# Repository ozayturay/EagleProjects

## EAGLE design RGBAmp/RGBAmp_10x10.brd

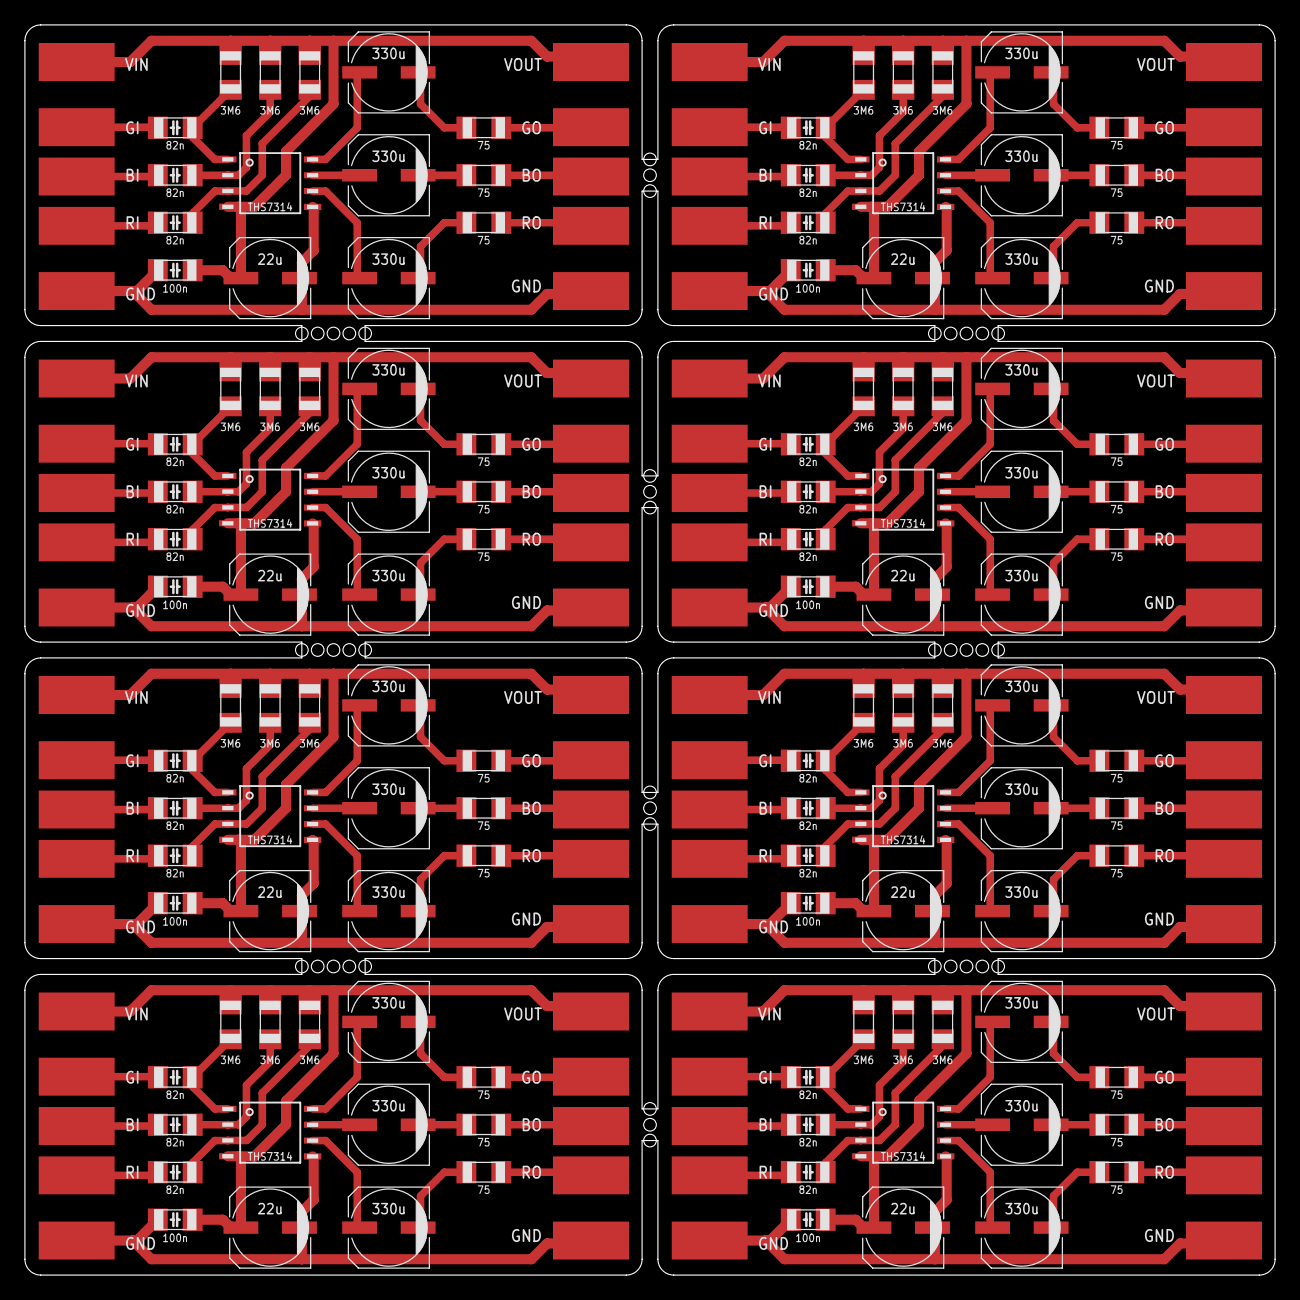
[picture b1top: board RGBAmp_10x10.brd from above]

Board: 2 copper layers, 100.3 x 100.3 mm, 144 parts (8 on the bottom side), 136 nets.

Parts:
C1, C2, C3, C9, C10, C11, C17, C18, C19, C25, C26, C27, C33, C34, C35, C41, C42, C43, C49, C50, C51, C57, C58, C59: 82n; CAPACITOR_CERAMIC_1206
C4, C5, C6, C12, C13, C14, C20, C21, C22, C28, C29, C30, C36, C37, C38, C44, C45, C46, C52, C53, C54, C60, C61, C62: 330u; CAPACITOR_POLARIZED_6.3X7.7
C7, C15, C23, C31, C39, C47, C55, C63: 100n; CAPACITOR_CERAMIC_1206
C8, C16, C24, C32, C40, C48, C56, C64: 22u; CAPACITOR_POLARIZED_6.3X7.7
CN1, CN3, CN5, CN7, CN9, CN11, CN13, CN15: INPUT; GBR_PADS
CN2, CN4, CN6, CN8, CN10, CN12, CN14, CN16: OUTPUT; GBR_PADS
LOGO1, LOGO2, LOGO3, LOGO4, LOGO5, LOGO6, LOGO7, LOGO8: OSHW_LOGO_SMALL
MCU1, MCU2, MCU3, MCU4, MCU5, MCU6, MCU7, MCU8: THS7314; SOP08
R1, R2, R3, R7, R8, R9, R13, R14, R15, R19, R20, R21, R25, R26, R27, R31, R32, R33, R37, R38, R39, R43, R44, R45: 3M6; RESISTOR_1206
R4, R5, R6, R10, R11, R12, R16, R17, R18, R22, R23, R24, R28, R29, R30, R34, R35, R36, R40, R41, R42, R46, R47, R48: 75; RESISTOR_1206

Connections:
GND: C7.2, C8.-, CN1.GND, CN2.GND, MCU1.5
GND1: C15.2, C16.-, CN3.GND, CN4.GND, MCU2.5
GND2: C23.2, C24.-, CN5.GND, CN6.GND, MCU3.5
GND3: C31.2, C32.-, CN7.GND, CN8.GND, MCU4.5
GND4: C39.2, C40.-, CN9.GND, CN10.GND, MCU5.5
GND5: C47.2, C48.-, CN11.GND, CN12.GND, MCU6.5
GND6: C55.2, C56.-, CN13.GND, CN14.GND, MCU7.5
GND7: C63.2, C64.-, CN15.GND, CN16.GND, MCU8.5
unnamed: C1.2, MCU1.1, R1.1
unnamed: C2.2, MCU1.2, R2.1
unnamed: C3.2, MCU1.3, R3.1
unnamed: C2.1, CN1.B
unnamed: C1.1, CN1.G
unnamed: C3.1, CN1.R
unnamed: C4.+, MCU1.8
unnamed: C5.+, MCU1.7
unnamed: C6.+, MCU1.6
unnamed: C4.-, R4.1
unnamed: C5.-, R5.1
unnamed: C6.-, R6.1
unnamed: CN2.G, R4.2
unnamed: CN2.B, R5.2
unnamed: CN2.R, R6.2
unnamed: C9.2, MCU2.1, R7.1
unnamed: C10.2, MCU2.2, R8.1
unnamed: C11.2, MCU2.3, R9.1
unnamed: C10.1, CN3.B
unnamed: C9.1, CN3.G
unnamed: C11.1, CN3.R
unnamed: C12.+, MCU2.8
unnamed: C13.+, MCU2.7
unnamed: C14.+, MCU2.6
unnamed: C12.-, R10.1
unnamed: C13.-, R11.1
unnamed: C14.-, R12.1
unnamed: CN4.G, R10.2
unnamed: CN4.B, R11.2
unnamed: CN4.R, R12.2
unnamed: C17.2, MCU3.1, R13.1
unnamed: C18.2, MCU3.2, R14.1
unnamed: C19.2, MCU3.3, R15.1
unnamed: C18.1, CN5.B
unnamed: C17.1, CN5.G
unnamed: C19.1, CN5.R
unnamed: C20.+, MCU3.8
unnamed: C21.+, MCU3.7
unnamed: C22.+, MCU3.6
unnamed: C20.-, R16.1
unnamed: C21.-, R17.1
unnamed: C22.-, R18.1
unnamed: CN6.G, R16.2
unnamed: CN6.B, R17.2
unnamed: CN6.R, R18.2
unnamed: C25.2, MCU4.1, R19.1
unnamed: C26.2, MCU4.2, R20.1
unnamed: C27.2, MCU4.3, R21.1
unnamed: C26.1, CN7.B
unnamed: C25.1, CN7.G
unnamed: C27.1, CN7.R
unnamed: C28.+, MCU4.8
unnamed: C29.+, MCU4.7
unnamed: C30.+, MCU4.6
unnamed: C28.-, R22.1
unnamed: C29.-, R23.1
unnamed: C30.-, R24.1
unnamed: CN8.G, R22.2
unnamed: CN8.B, R23.2
unnamed: CN8.R, R24.2
unnamed: C33.2, MCU5.1, R25.1
unnamed: C34.2, MCU5.2, R26.1
unnamed: C35.2, MCU5.3, R27.1
unnamed: C34.1, CN9.B
unnamed: C33.1, CN9.G
unnamed: C35.1, CN9.R
unnamed: C36.+, MCU5.8
unnamed: C37.+, MCU5.7
unnamed: C38.+, MCU5.6
unnamed: C36.-, R28.1
unnamed: C37.-, R29.1
unnamed: C38.-, R30.1
unnamed: CN10.G, R28.2
unnamed: CN10.B, R29.2
unnamed: CN10.R, R30.2
unnamed: C41.2, MCU6.1, R31.1
unnamed: C42.2, MCU6.2, R32.1
unnamed: C43.2, MCU6.3, R33.1
unnamed: C42.1, CN11.B
unnamed: C41.1, CN11.G
unnamed: C43.1, CN11.R
unnamed: C44.+, MCU6.8
unnamed: C45.+, MCU6.7
unnamed: C46.+, MCU6.6
unnamed: C44.-, R34.1
unnamed: C45.-, R35.1
unnamed: C46.-, R36.1
unnamed: CN12.G, R34.2
unnamed: CN12.B, R35.2
unnamed: CN12.R, R36.2
unnamed: C49.2, MCU7.1, R37.1
unnamed: C50.2, MCU7.2, R38.1
unnamed: C51.2, MCU7.3, R39.1
unnamed: C50.1, CN13.B
unnamed: C49.1, CN13.G
unnamed: C51.1, CN13.R
unnamed: C52.+, MCU7.8
unnamed: C53.+, MCU7.7
unnamed: C54.+, MCU7.6
unnamed: C52.-, R40.1
unnamed: C53.-, R41.1
unnamed: C54.-, R42.1
unnamed: CN14.G, R40.2
unnamed: CN14.B, R41.2
unnamed: CN14.R, R42.2
unnamed: C57.2, MCU8.1, R43.1
unnamed: C58.2, MCU8.2, R44.1
unnamed: C59.2, MCU8.3, R45.1
unnamed: C58.1, CN15.B
unnamed: C57.1, CN15.G
unnamed: C59.1, CN15.R
unnamed: C60.+, MCU8.8
unnamed: C61.+, MCU8.7
unnamed: C62.+, MCU8.6
unnamed: C60.-, R46.1
unnamed: C61.-, R47.1
unnamed: C62.-, R48.1
unnamed: CN16.G, R46.2
unnamed: CN16.B, R47.2
unnamed: CN16.R, R48.2
VCC: C7.1, C8.+, CN1.VCC, CN2.VCC, MCU1.4, R1.2, R2.2, R3.2
VCC1: C15.1, C16.+, CN3.VCC, CN4.VCC, MCU2.4, R7.2, R8.2, R9.2
VCC2: C23.1, C24.+, CN5.VCC, CN6.VCC, MCU3.4, R13.2, R14.2, R15.2
VCC3: C31.1, C32.+, CN7.VCC, CN8.VCC, MCU4.4, R19.2, R20.2, R21.2
VCC4: C39.1, C40.+, CN9.VCC, CN10.VCC, MCU5.4, R25.2, R26.2, R27.2
VCC5: C47.1, C48.+, CN11.VCC, CN12.VCC, MCU6.4, R31.2, R32.2, R33.2
VCC6: C55.1, C56.+, CN13.VCC, CN14.VCC, MCU7.4, R37.2, R38.2, R39.2
VCC7: C63.1, C64.+, CN15.VCC, CN16.VCC, MCU8.4, R43.2, R44.2, R45.2

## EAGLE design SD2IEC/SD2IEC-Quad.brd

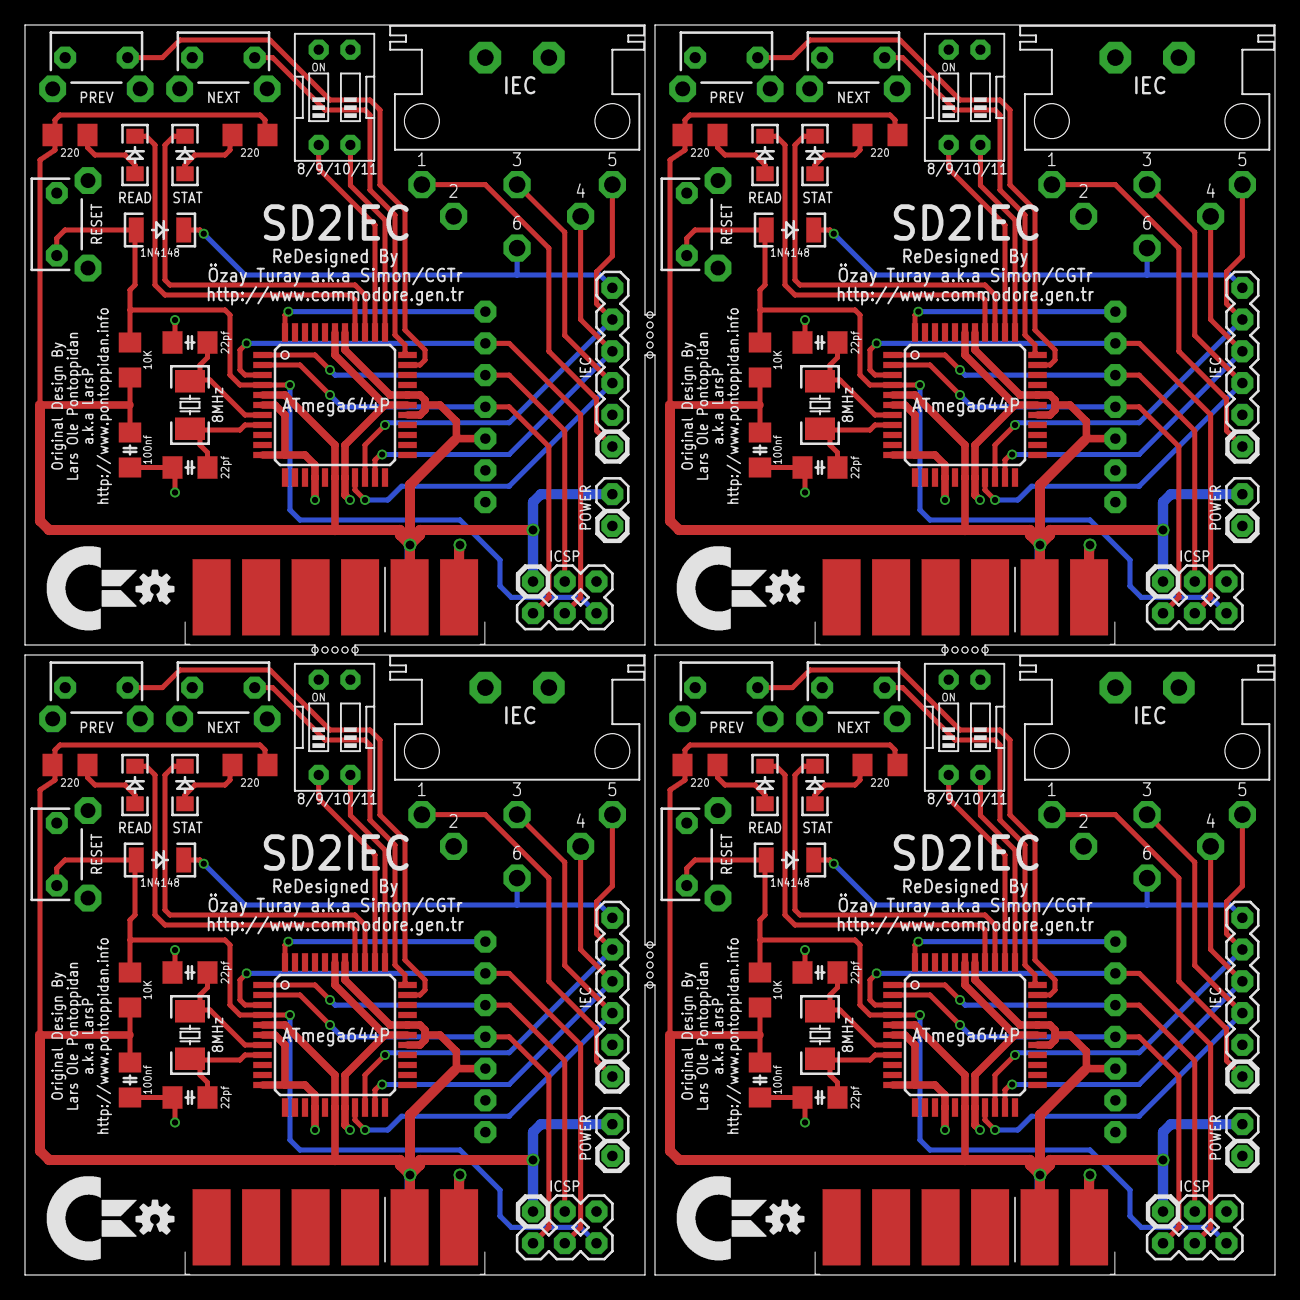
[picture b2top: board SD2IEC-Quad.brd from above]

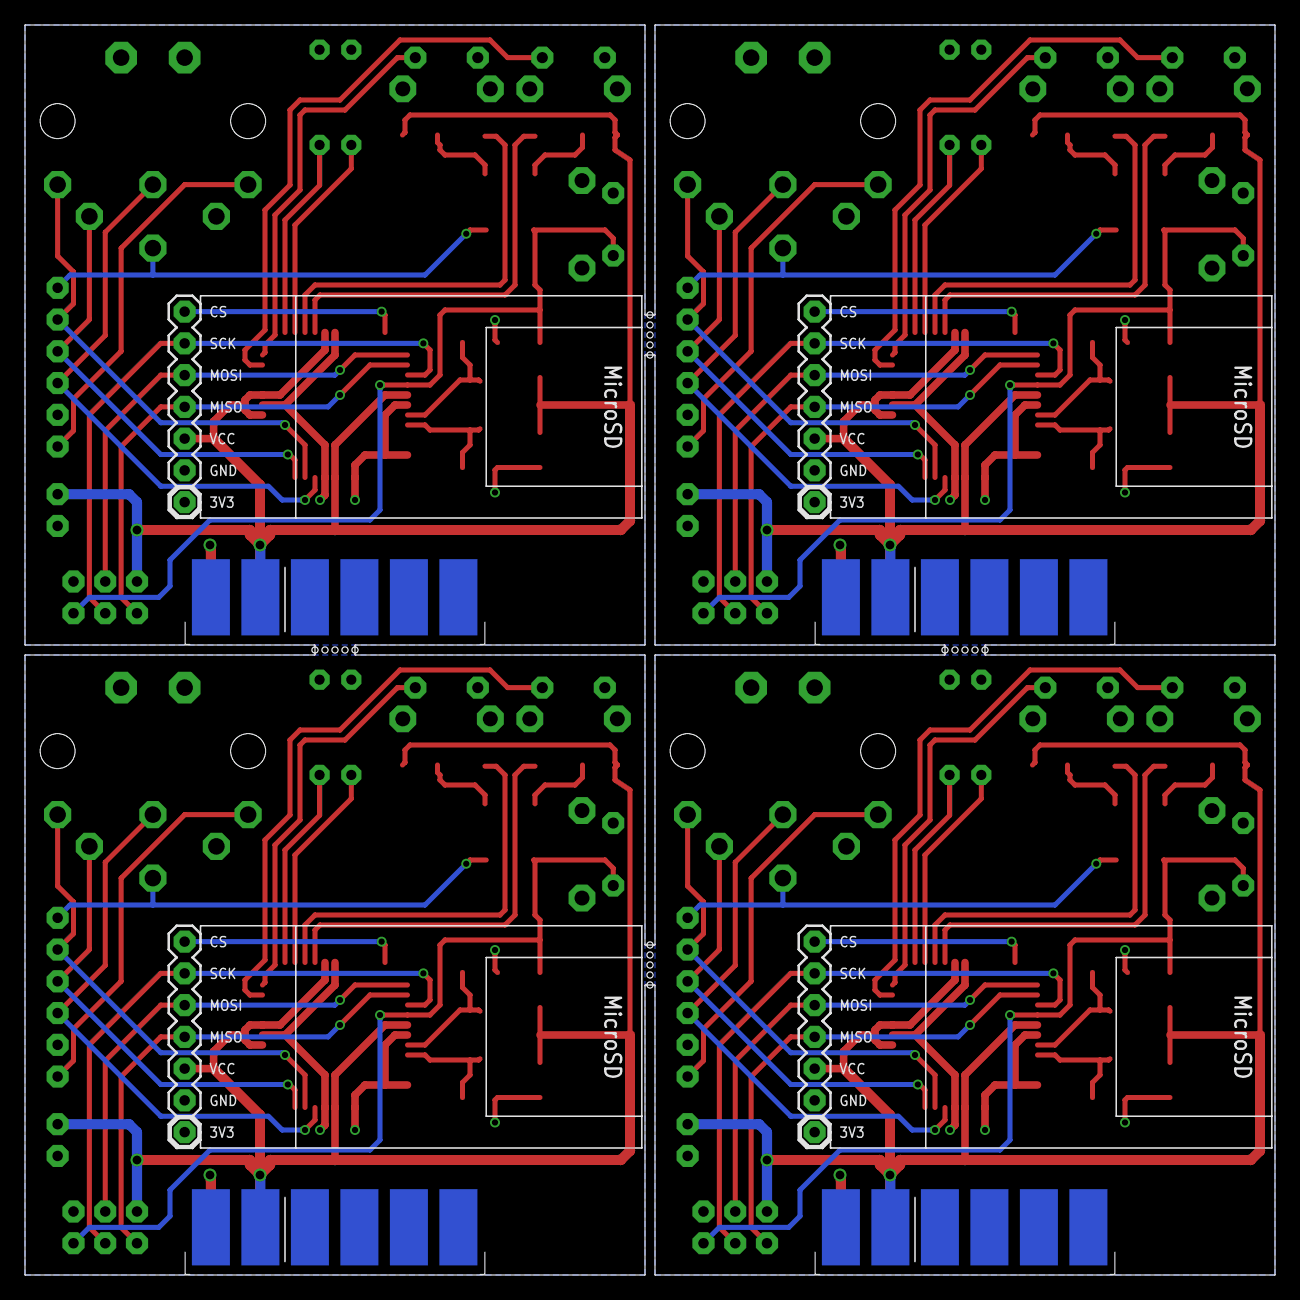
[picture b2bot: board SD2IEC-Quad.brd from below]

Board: 2 copper layers, 100.0 x 100.0 mm, 88 parts (4 on the bottom side), 88 nets.

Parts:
C1, C4, C7, C10: 100nf; CAPACITOR_CERAMIC_1206
C2, C3, C5, C6, C8, C9, C11, C12: 22pf; CAPACITOR_CERAMIC_1206
CN1, CN2, CN3, CN4: DATASETTE; C64_DATASETTE_PADS
D1, D2, D3, D4: 1N4148; DIODE_NORMAL_SMT
J1, J6, J10, J14: POWER; HDR_1X02
J2, J7, J11, J15: IEC; HDR_1X06
J3, J8, J12, J16: ICSP; HDR_2X03
J4, J5, J9, J13: IEC; C64_IEC_DIN6
LED1, LED3, LED5, LED7: STAT; LED_1206
LED2, LED4, LED6, LED8: READ; LED_1206
LOGO1, LOGO2, LOGO3, LOGO4: OSHW_LOGO_SMALL
MCU, MCU1, MCU2, MCU3: ATmega644P; TQFP44
R1, R2, R4, R5, R7, R8, R10, R11: 220; RESISTOR_1206
R3, R6, R9, R12: 10K; RESISTOR_1206
SD, SD1, SD2, SD3: MicroSD; MICROSD_RTL
SW1, SW5, SW9, SW13: NEXT; SWITCH_THT_SIDE
SW2, SW6, SW10, SW14: PREV; SWITCH_THT_SIDE
SW3, SW7, SW11, SW15: RESET; SWITCH_THT_SIDE
SW4, SW8, SW12, SW16: 8/9/10/11; SWITCH_DIP_02
XTAL, XTAL1, XTAL2, XTAL3: 8MHz; XTAL_5032

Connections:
8/1: MCU1.35, SW8.1
8/2: MCU2.35, SW12.1
8/3: MCU3.35, SW16.1
8/9: MCU.35, SW4.1
10/1: MCU1.34, SW8.2
10/2: MCU2.34, SW12.2
10/3: MCU3.34, SW16.2
10/11: MCU.34, SW4.2
CS: MCU.44, SD.CS
CS1: MCU1.44, SD1.CS
CS2: MCU2.44, SD2.CS
CS3: MCU3.44, SD3.CS
GND: C1.1, C2.1, C3.1, CN1.1, CN1.A, J1.1, J2.2, J3.3, J4.2, MCU.6, MCU.11, MCU.15, MCU.18, MCU.28, MCU.39, SD.GND, SW1.2, SW2.2, SW3.1, SW4.3, SW4.4
GND1: C4.1, C5.1, C6.1, CN2.1, CN2.A, J5.2, J6.1, J7.2, J8.3, MCU1.6, MCU1.11, MCU1.15, MCU1.18, MCU1.28, MCU1.39, SD1.GND, SW5.2, SW6.2, SW7.1, SW8.3, SW8.4
GND2: C7.1, C8.1, C9.1, CN3.1, CN3.A, J9.2, J10.1, J11.2, J12.3, MCU2.6, MCU2.11, MCU2.15, MCU2.18, MCU2.28, MCU2.39, SD2.GND, SW9.2, SW10.2, SW11.1, SW12.3, SW12.4
GND3: C10.1, C11.1, C12.1, CN4.1, CN4.A, J13.2, J14.1, J15.2, J16.3, MCU3.6, MCU3.11, MCU3.15, MCU3.18, MCU3.28, MCU3.39, SD3.GND, SW13.2, SW14.2, SW15.1, SW16.3, SW16.4
IEC_ATN: J2.3, J4.3, MCU.19
IEC_ATN1: J5.3, J7.3, MCU1.19
IEC_ATN2: J9.3, J11.3, MCU2.19
IEC_ATN3: J13.3, J15.3, MCU3.19
IEC_CLK: J2.4, J4.4, MCU.21
IEC_CLK1: J5.4, J7.4, MCU1.21
IEC_CLK2: J9.4, J11.4, MCU2.21
IEC_CLK3: J13.4, J15.4, MCU3.21
IEC_DATA: J2.5, J4.5, MCU.20
IEC_DATA1: J5.5, J7.5, MCU1.20
IEC_DATA2: J9.5, J11.5, MCU2.20
IEC_DATA3: J13.5, J15.5, MCU3.20
IEC_RST: D1.C, J2.6, J4.6
IEC_RST1: D2.C, J5.6, J7.6
IEC_RST2: D3.C, J9.6, J11.6
IEC_RST3: D4.C, J13.6, J15.6
IEC_SRQ: J2.1, J4.1
IEC_SRQ1: J5.1, J7.1
IEC_SRQ2: J9.1, J11.1
IEC_SRQ3: J13.1, J15.1
MISO: J3.4, MCU.2, SD.MISO
MISO1: J8.4, MCU1.2, SD1.MISO
MISO2: J12.4, MCU2.2, SD2.MISO
MISO3: J16.4, MCU3.2, SD3.MISO
MOSI: J3.2, MCU.1, SD.MOSI
MOSI1: J8.2, MCU1.1, SD1.MOSI
MOSI2: J12.2, MCU2.1, SD2.MOSI
MOSI3: J16.2, MCU3.1, SD3.MOSI
NEXT: MCU.33, SW1.1
NEXT1: MCU1.33, SW5.1
NEXT2: MCU2.33, SW9.1
NEXT3: MCU3.33, SW13.1
PREV: MCU.32, SW2.1
PREV1: MCU1.32, SW6.1
PREV2: MCU2.32, SW10.1
PREV3: MCU3.32, SW14.1
READ: LED2.C, MCU.37
READ1: LED2.A, R2.1
READ2: LED4.C, MCU1.37
READ3: LED4.A, R5.1
READ4: LED6.C, MCU2.37
READ5: LED6.A, R8.1
READ6: LED8.C, MCU3.37
READ7: LED8.A, R11.1
RST: D1.A, J3.6, MCU.4, R3.2, SW3.2
RST1: D2.A, J8.6, MCU1.4, R6.2, SW7.2
RST2: D3.A, J12.6, MCU2.4, R9.2, SW11.2
RST3: D4.A, J16.6, MCU3.4, R12.2, SW15.2
SCK: J3.5, MCU.3, SD.SCK
SCK1: J8.5, MCU1.3, SD1.SCK
SCK2: J12.5, MCU2.3, SD2.SCK
SCK3: J16.5, MCU3.3, SD3.SCK
SELECT: LED1.C, MCU.36
SELECT1: LED1.A, R1.1
SELECT2: LED3.C, MCU1.36
SELECT3: LED3.A, R4.1
SELECT4: LED5.C, MCU2.36
SELECT5: LED5.A, R7.1
SELECT6: LED7.C, MCU3.36
SELECT7: LED7.A, R10.1
VCC: C1.2, CN1.2, CN1.B, J1.2, J3.1, MCU.5, MCU.17, MCU.27, MCU.29, MCU.38, R1.2, R2.2, R3.1, SD.VCC
VCC1: C4.2, CN2.2, CN2.B, J6.2, J8.1, MCU1.5, MCU1.17, MCU1.27, MCU1.29, MCU1.38, R4.2, R5.2, R6.1, SD1.VCC
VCC2: C7.2, CN3.2, CN3.B, J10.2, J12.1, MCU2.5, MCU2.17, MCU2.27, MCU2.29, MCU2.38, R7.2, R8.2, R9.1, SD2.VCC
VCC3: C10.2, CN4.2, CN4.B, J14.2, J16.1, MCU3.5, MCU3.17, MCU3.27, MCU3.29, MCU3.38, R10.2, R11.2, R12.1, SD3.VCC
XTAL1: C2.2, MCU.8, XTAL.1
XTAL2: C3.2, MCU.7, XTAL.2
XTAL3: C5.2, MCU1.8, XTAL1.1
XTAL4: C6.2, MCU1.7, XTAL1.2
XTAL5: C8.2, MCU2.8, XTAL2.1
XTAL6: C9.2, MCU2.7, XTAL2.2
XTAL7: C11.2, MCU3.8, XTAL3.1
XTAL8: C12.2, MCU3.7, XTAL3.2

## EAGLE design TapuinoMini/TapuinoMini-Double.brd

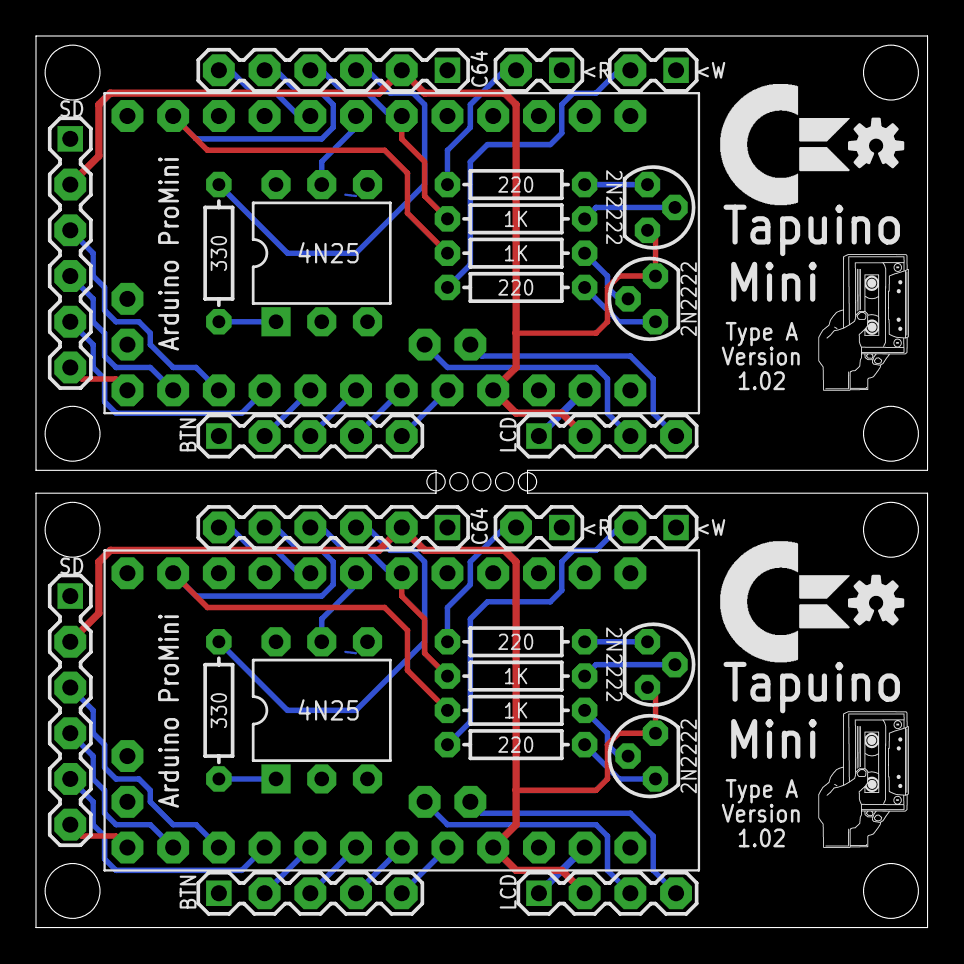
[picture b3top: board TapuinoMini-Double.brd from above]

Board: 2 copper layers, 49.5 x 49.5 mm, 32 parts (0 on the bottom side), 48 nets.

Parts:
IC1, IC2: Arduino ProMini; PROMINI_A
JP1, JP7: LCD; 1X04_SQR
JP2, JP8: SD; 1X06_SQR
JP3, JP9: BTN; 1X05_SQR
JP4, JP10: C64; 1X06_SQR
JP5, JP11: <R; 1X02_SQR
JP6, JP12: <W; 1X02_SQR
OK1, OK2: 4N25; DIP06
Q1, Q2, Q3, Q4: 2N2222; TO-92
R1, R2, R7, R8: 1K; RESISTOR_PTH_0.3
R3, R4, R9, R10: 220; RESISTOR_PTH_0.3
R5, R6: 330; RESISTOR_PTH_0.3
U$1, U$3: OSHW-LOGO-S

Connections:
ABORT: IC1.A2, JP3.4
ABORT1: IC2.A2, JP9.4
CS: IC1.10*, JP2.6
CS1: IC2.10*, JP8.6
GND: IC1.GND@1, JP1.1, JP2.1, JP3.1, JP4.1, JP5.1, JP6.1, OK1.2, OK1.4
GND1: IC2.GND@1, JP7.1, JP8.1, JP9.1, JP10.1, JP11.1, JP12.1, OK2.2, OK2.4
MISO: IC1.12, JP2.3
MISO1: IC2.12, JP8.3
MOSI: IC1.11*, JP2.4
MOSI1: IC2.11*, JP8.4
MOTOR1: JP4.3, R5.1
MOTOR2: OK1.1, R5.2
MOTOR3: IC1.4, OK1.5
MOTOR4: JP10.3, R6.1
MOTOR5: OK2.1, R6.2
MOTOR6: IC2.4, OK2.5
NEXT: IC1.A0, JP3.2
NEXT1: IC2.A0, JP9.2
PREV: IC1.A1, JP3.3
PREV1: IC2.A1, JP9.3
READ1: IC1.3*, JP4.4, R1.1
READ2: Q1.2, R1.2
READ3: Q1.1, R3.1
READ4: JP5.2, R3.2
READ5: IC2.3*, JP10.4, R7.1
READ6: Q3.2, R7.2
READ7: Q3.1, R9.1
READ8: JP11.2, R9.2
SCK: IC1.13, JP2.5
SCK1: IC2.13, JP8.5
SCL: IC1.A5, JP1.4
SCL1: IC2.A5, JP7.4
SDA: IC1.A4, JP1.3
SDA1: IC2.A4, JP7.3
SELECT: IC1.A3, JP3.5
SELECT1: IC2.A3, JP9.5
SENSE: IC1.5*, JP4.6
SENSE1: IC2.5*, JP10.6
VCC: IC1.VCC, JP1.2, JP2.2, JP4.2, Q1.3, Q2.3
VCC1: IC2.VCC, JP7.2, JP8.2, JP10.2, Q3.3, Q4.3
WRITE1: IC1.8, JP4.5, R2.1
WRITE2: Q2.2, R2.2
WRITE3: Q2.1, R4.1
WRITE4: JP6.2, R4.2
WRITE5: IC2.8, JP10.5, R8.1
WRITE6: Q4.2, R8.2
WRITE7: Q4.1, R10.1
WRITE8: JP12.2, R10.2

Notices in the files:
parts and their libraries:
SparkFun-Aesthetics: Licensing: Creative Commons ShareAlike 4.0 International - https://creativecommons.org/licenses/by-sa/4.0
